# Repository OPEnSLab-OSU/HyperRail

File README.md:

# Hyperspectral_Camera
Repository for the HyperRail and HyperPole Projects

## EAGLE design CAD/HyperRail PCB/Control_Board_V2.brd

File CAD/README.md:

This folder contains all the links to all the 3D printed pieces used on the HyperRail: 

[Hyspectral Camera Housing](http://a360.co/2D8uV4A) 
[Line Gear](http://a360.co/2Hfb8TT) 
[Line Tie}(http://a360.co/2oWLrj7)
[Idling Pully Assembly](http://a360.co/2oWLrj7) 
[Motor Mount](http://a360.co/2FpC4j6)

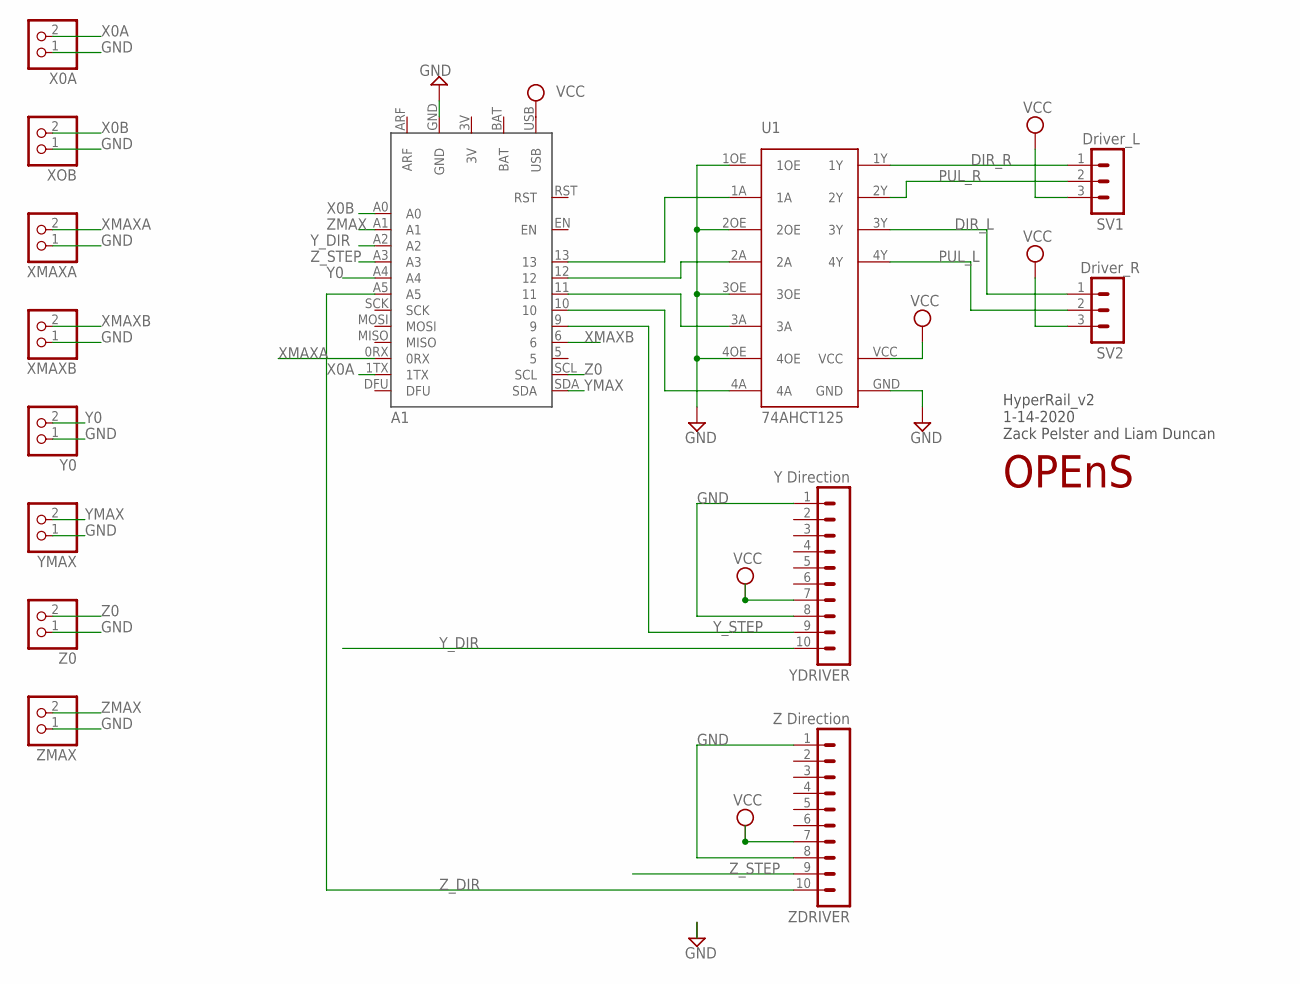
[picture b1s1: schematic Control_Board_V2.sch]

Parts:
A1: FEATHER_BLUEFRUIT_M0
SV1: Driver_L; MA03-1
SV2: Driver_R; MA03-1
U1: 74AHCT125
U$1: OPENS-LOGO
X0A: PINHD-1X2; 1X02
XMAXA: PINHD-1X2; 1X02
XMAXB: PINHD-1X2; 1X02
XOB: PINHD-1X2; 1X02
Y0: PINHD-1X2; 1X02
YDRIVER: Y Direction; MA10-1
YMAX: PINHD-1X2; 1X02
Z0: PINHD-1X2; 1X02
ZDRIVER: Z Direction; MA10-1
ZMAX: PINHD-1X2; 1X02

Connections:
3V: A1.3V
BAT: A1.BAT
DIR_L: SV2.1, U1.3Y
DIR_R: SV1.1, U1.1Y
GND: A1.GND, U1.1OE, U1.2OE, U1.3OE, U1.4OE, U1.GND, X0A.1, XMAXA.1, XMAXB.1, XOB.1, Y0.1, YDRIVER.1, YDRIVER.8, YMAX.1, Z0.1, ZDRIVER.1, ZDRIVER.8, ZMAX.1
unnamed: A1.13, U1.1A
unnamed: A1.12, U1.2A
unnamed: A1.11, U1.3A
unnamed: A1.10, U1.4A
PUL_L: SV2.2, U1.4Y
PUL_R: SV1.2, U1.2Y
VCC: A1.USB, SV1.3, SV2.3, U1.VCC, YDRIVER.7, ZDRIVER.7
X0A: A1.1TX, X0A.2
X0B: A1.A0, XOB.2
XMAXA: A1.0RX, XMAXA.2
XMAXB: A1.6, XMAXB.2
Y0: A1.A4, Y0.2
YMAX: A1.SDA, YMAX.2
Y_DIR: A1.A2, YDRIVER.10
Y_STEP: A1.9, YDRIVER.9
Z0: A1.SCL, Z0.2
ZMAX: A1.A1, ZMAX.2
Z_DIR: A1.A5, ZDRIVER.10
Z_STEP: A1.A3, ZDRIVER.9

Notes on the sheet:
HyperRail_v2 1-14-2020 Zack Pelster and Liam Duncan

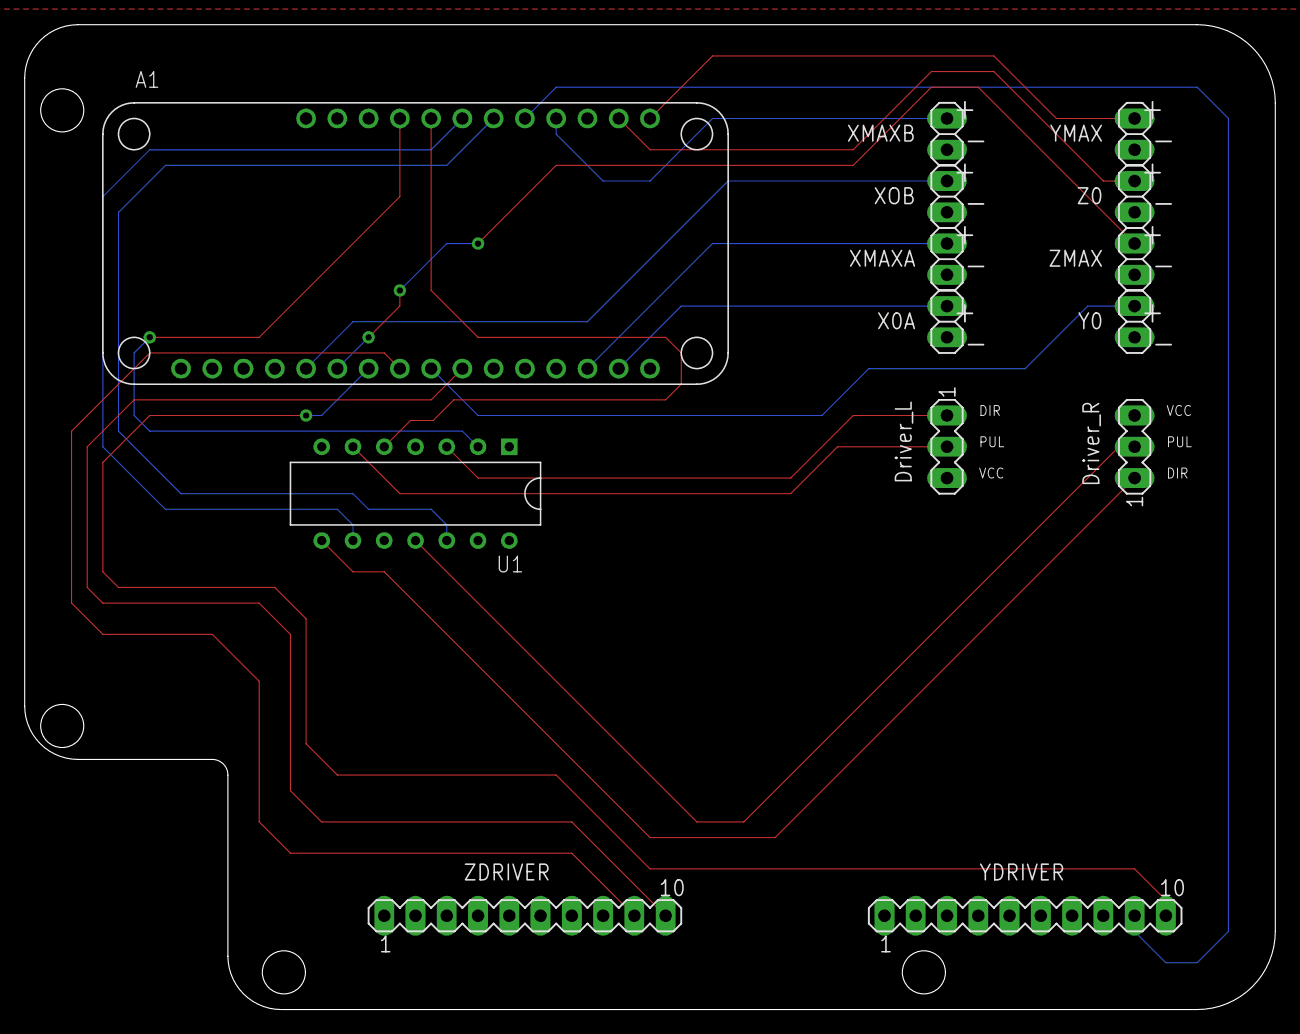
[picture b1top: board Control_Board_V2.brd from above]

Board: 2 copper layers, 101.6 x 80.0 mm, 15 parts (1 on the bottom side), 22 nets.

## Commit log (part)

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2017-09-01 Create FolderDescription
2017-09-01 Rename FolderDescription to ReadMe.md
2017-09-01 Rename ReadMe.md to README.md
2017-09-01 Create TestCode
    This code was used to test the hyper rails
2017-09-15 Create HyperRail_RPM_Control
2017-09-15 Rename Code/HyperRail_RPM_Control to HyperRail/Code/HyperRail_RPM_Control
2018-01-22 Create HyperRail_impl
2018-01-22 Rename Code/TestCode to Code/Driver Test Code/Big Easy Driver Ex. Code
2018-01-22 Rename HyperRail_impl to HyperRail_implemented
2018-01-22 Create HOLD
2018-02-03 Add files via upload
    These two files are the first working version of the HyperRail GUI. Both must be used for HyeperRail to work.
2018-03-07 Rename LINKS.md to 3DPrinted.md
2018-03-07 Rename Attechements.md to Attachments.md
2018-03-28 Rename Code/GUI/HyperRail_GUI.ino to Code/GUI/Arduino_UNO/HyperRail_GUI.ino
2018-03-28 Rename Code/GUI/HyperRailGUI3.pde to Code/GUI/Arduino_UNO/HyperRailGUI3.pde
2018-03-28 Create testfile
2018-03-28 Add files via upload
    This new sketch is a modified version of the original file that will work with the Feather M0 LoRa micrcontroller
2018-09-04 Rename 3DPrinted.md to 3DPrinted_Pages.md
2018-09-04 Create TEXT
2018-09-04 Rename Attachments.md to Attachments_Pages.md
2018-09-14 Rename WiringDiagram.md to WiringDiagram/WiringDiagram.md
2018-09-14 Rename WiringDiagram.md to README.md
2018-12-03 added progress report
2019-01-07 Add files via upload
    These are the STL files for the electronics enclosure
2019-02-02 Moved functions to routes. db is no longer global variable.
2019-02-02 Initial experiments with server. Currently using NodeJS and MongoDB
2019-02-02 Removed MongoDB, using InfluxDB now. Removed users endpoints. Added files for config endpoint. Fleshed out runs endpoints.
2019-02-02 Added configs endpoints. Fixing up dependencies
2019-02-02 Added timestamps to logs
2019-02-02 Added dynamic searches
2019-02-02 Current UI Stuff
    Pushed Current UI Stuff
2019-02-02 Move ui to public folder
2019-02-02 Added some comments
2019-02-05 Adding linter to project
2019-02-05 Make linter happy
2019-02-05 Organized public folder
2019-02-05 Ignore dependencies in linter
2019-02-05 Redirects Empty Url to Home
2019-02-05 Linked Up the Search to the Server
    Can now query the server/database for data collected.
2019-02-05 Fixed query for runs based on run name
2019-02-05 Fix timestamp to be current timezone
2019-02-05 Small table changes
2019-02-15 Intial work with bot code
2019-02-15 Building up arduino code further
2019-02-18 Continuing progress
2019-02-21 Add files via upload
    This is the latest version of the code that works with the M0.
2019-02-21 Add files via upload
    This is the accompanying file that goes with the Arduino sketch. They must be used together for the system to work.
2019-02-23 Added code to create configuration and load configurations
    Not sure if code works, unable to test.
2019-03-06 Working on bot connections
2019-03-06 Configs can now modify saved configurations
2019-03-06 Updated UI styling to make it more pleasing
2019-03-12 Some CSS changes
2019-03-12 Fixed a bug in the runs page
2019-03-12 Changed content sizing and text
2019-03-13 Query Bug officially fixed
    Can now perform empty and non-empty query searches
2019-03-13 Added Sensor.json file
2019-03-13 Some styling changes for query form
2019-03-13 Fixed server interaction. Now retrieves list of configs and sensors.
    Still trying to get create configs to work properly
2019-03-14 Styling changes
2019-03-14 Working on sending bundles back to HyperRail app in json format
2019-03-15 Working on updating config format
2019-03-15 Added support for uploading config to bot
2019-03-15 Changing schema a bit
2019-03-15 Working on connecting up WiFi
2019-03-15 Can now create and edit configurations.
2019-03-17 Removed Some Test files
2019-03-17 Small Style Changes
2019-03-17 Added ability to limit number of rows displayed
2019-03-17 Can now Delete Configs, more documentation and fixes
2019-03-17 Working on formatting sensor data
2019-03-17 Config Bugs fixed
2019-03-17 Can Now Execute Runs
2019-03-17 Can now search to match or contain filters
2019-03-18 Added Winter progress reports
2019-03-18 Finish work on integrating WiFi. Bugs included.
2019-03-18 Modify data schema
2019-03-18 Removed MongoDB, using InfluxDB now. Removed users endpoints. Added files for config endpoint. Fleshed out runs endpoints.
    Added configs endpoints. Fixing up dependencies
    Added timestamps to logs
    Added dynamic searches
    Current UI Stuff
    Pushed Current UI Stuff
    Move ui to public folder
2019-03-18 Adding linter to project
    Make linter happy
    Organized public folder
    Ignore dependencies in linter
    Change comment rules
    Redirects Empty Url to Home
    Linked Up the Search to the Server
2019-03-18 Intial work with bot code
    Small table changes
    Building up arduino code further
    More work on Configs
    Can add more sensor fields to form, added error messages.
    Continuing progress
    Added code to create configuration and load configurations
2019-03-18 Configs can now modify saved configurations
    Updated UI styling to make it more pleasing
    Some CSS changes
    Fixed a bug in the runs page
2019-03-18 Changed content sizing and text
    Fixed logging error
    Query Bug officially fixed
    Can now perform empty and non-empty query searches
2019-03-18 Added support for uploading config to bot
    Changing schema a bit
2019-03-18 Working on connecting up WiFi
    Can now create and edit configurations.
    Random Test Configs
    Removed Some Test files
2019-03-18 Added ability to limit number of rows displayed
    Can now Delete Configs, more documentation and fixes
    Working on formatting sensor data
    Working on Trying to Execute Runs from UI
    Config Bugs fixed
    Can Now Execute Runs
2019-03-18 Finish work on integrating WiFi. Bugs included.
    Modify data schema
2019-04-03 Cleaning up code
2019-04-04 Added Logo to UI
2019-04-09 Simplify and format database response
2019-04-09 Added live data endpoint
2019-04-09 Data Display Fixed and Changed to Fit Schema
2019-04-09 Fixed Data Display
2019-04-09 Adjusted Text Size, Added Scrollbars
2019-04-11 Tested config CRUD
2019-04-11 Modified Fields to match Processing GUI
2019-04-11 Modified code to match processing GUI stuff. Added failed execution alert.
2019-04-11 Some comments to clarify configs
2019-04-11 Calculated needed values for bot execution
2019-04-14 Mocked sensor response for expo
2019-04-15 Added step to connect to Wifi
2019-04-16 Added reports
2019-04-29 Document Revisions Signed
2019-05-15 Fixed directional pins and rail length input
2019-05-21 Removed unnecessary delay. Changed Testing configuration for the Expo
2019-06-06 Project Hand Off Documentation
2019-10-21 Delete Roller4.stl
    I changed the name to match the name given in the paper submission
2019-10-21 Bump axios from 0.18.0 to 0.18.1 in /Code/server
    Bumps [axios](https://github.com/axios/axios) from 0.18.0 to 0.18.1.
    - [Release notes](https://github.com/axios/axios/releases)
    - [Changelog](https://github.com/axios/axios/blob/v0.18.1/CHANGELOG.md)
    - [Commits](https://github.com/axios/axios/compare/v0.18.0...v0.18.1)
2019-10-21 Bump js-yaml from 3.12.1 to 3.13.1 in /Code/server
    Bumps [js-yaml](https://github.com/nodeca/js-yaml) from 3.12.1 to 3.13.1.
    - [Release notes](https://github.com/nodeca/js-yaml/releases)
    - [Changelog](https://github.com/nodeca/js-yaml/blob/master/CHANGELOG.md)
    - [Commits](https://github.com/nodeca/js-yaml/compare/3.12.1...3.13.1)
2019-10-21 Bump eslint-utils from 1.3.1 to 1.4.3 in /Code/server
    Bumps [eslint-utils](https://github.com/mysticatea/eslint-utils) from 1.3.1 to 1.4.3.
    - [Release notes](https://github.com/mysticatea/eslint-utils/releases)
    - [Commits](https://github.com/mysticatea/eslint-utils/compare/v1.3.1...v1.4.3)
2020-02-25 New Simpler Code added as well as Bump Switch Demo
2020-02-25 PCB Files added
2020-03-14 Bump acorn from 6.0.7 to 6.4.1 in /Code/server
    Bumps [acorn](https://github.com/acornjs/acorn) from 6.0.7 to 6.4.1.
    - [Release notes](https://github.com/acornjs/acorn/releases)
    - [Commits](https://github.com/acornjs/acorn/compare/6.0.7...6.4.1)
2020-04-24 New file added that uses accelstepper library
2020-04-24 added acceleration control
2020-04-24 deleted extra file
2020-05-01 Accelstepper code is now fully functional with acceleration control
2020-05-01 Velocity control from Processing will now work
2020-05-02 HyperRail Web App Started
2020-05-02 web app started
2020-05-02 css file added and serial port interface started
2020-05-06 Added Microstep variable to fix the mm to steps calculation for Y,Z Motors
2020-05-06 Added some comments for the microstep variables
2020-05-13 updated bump switch demo
2020-05-21 Interrupts
2020-05-22 added delay
2020-05-29 deLoomify
2020-05-29 fixed loom error
2020-06-05 deloomed bump switch demo
2020-06-08 Bump switch demo not only registers switches on press and not release
2020-06-25 Fixed some Variable names
2020-06-26 Fixed Loop
2020-06-29 calibration function updated
2020-06-29 Removed autosave file
2020-07-01 Updated GUI
2020-07-08 Split the Driver code into three different files for ease of use and added comments
2020-07-08 Removed old code
2021-01-05 Bump axios from 0.18.0 to 0.21.1 in /Code/server
    Bumps [axios](https://github.com/axios/axios) from 0.18.0 to 0.21.1.
    - [Release notes](https://github.com/axios/axios/releases)
    - [Changelog](https://github.com/axios/axios/blob/v0.21.1/CHANGELOG.md)
    - [Commits](https://github.com/axios/axios/compare/v0.18.0...v0.21.1)
2021-05-08 Bump lodash from 4.17.11 to 4.17.21 in /Code/server
    Bumps [lodash](https://github.com/lodash/lodash) from 4.17.11 to 4.17.21.
    - [Release notes](https://github.com/lodash/lodash/releases)
    - [Commits](https://github.com/lodash/lodash/compare/4.17.11...4.17.21)
2022-01-13 Bump follow-redirects from 1.6.1 to 1.14.7 in /Code/server
    Bumps [follow-redirects](https://github.com/follow-redirects/follow-redirects) from 1.6.1 to 1.14.7.
    - [Release notes](https://github.com/follow-redirects/follow-redirects/releases)
    - [Commits](https://github.com/follow-redirects/follow-redirects/compare/v1.6.1...v1.14.7)
    ---
    updated-dependencies:
    - dependency-name: follow-redirects
2022-02-11 Bump ajv from 6.8.1 to 6.12.6 in /Code/server
    Bumps [ajv](https://github.com/ajv-validator/ajv) from 6.8.1 to 6.12.6.
    - [Release notes](https://github.com/ajv-validator/ajv/releases)
    - [Commits](https://github.com/ajv-validator/ajv/compare/v6.8.1...v6.12.6)
    ---
    updated-dependencies:
    - dependency-name: ajv
2022-02-12 Bump follow-redirects from 1.6.1 to 1.14.8 in /Code/server
    Bumps [follow-redirects](https://github.com/follow-redirects/follow-redirects) from 1.6.1 to 1.14.8.
    - [Release notes](https://github.com/follow-redirects/follow-redirects/releases)
    - [Commits](https://github.com/follow-redirects/follow-redirects/compare/v1.6.1...v1.14.8)
    ---
    updated-dependencies:
    - dependency-name: follow-redirects
